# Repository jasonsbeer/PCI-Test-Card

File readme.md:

A card to connect test equipment to a 5V/Universal PCI bus slot.

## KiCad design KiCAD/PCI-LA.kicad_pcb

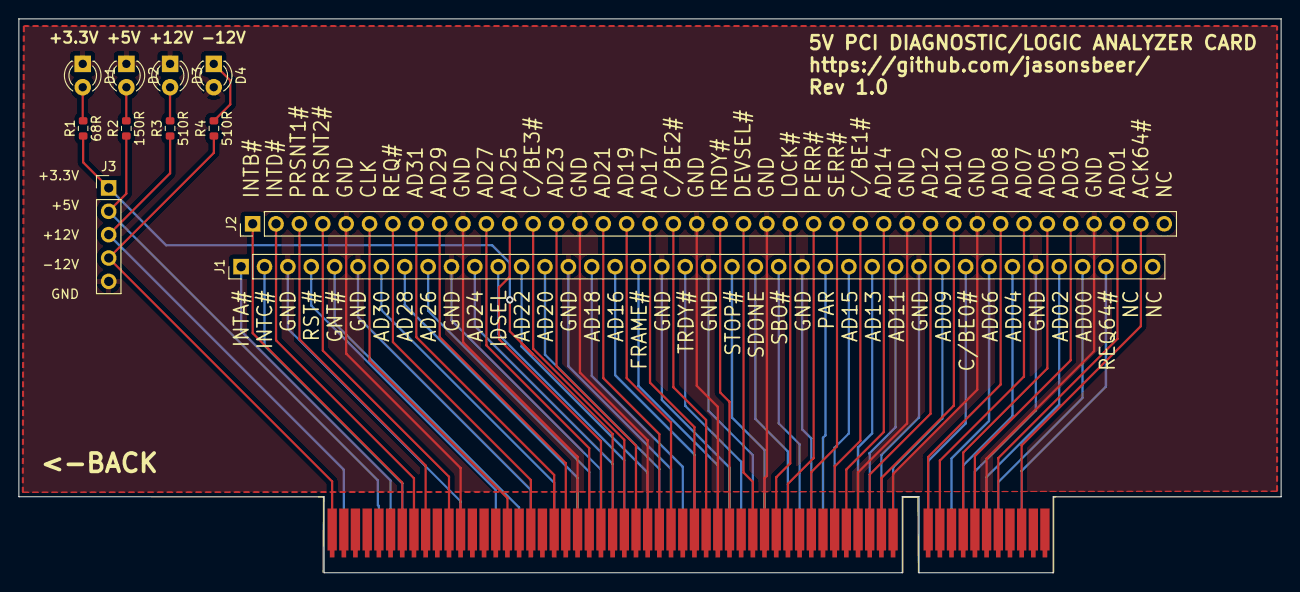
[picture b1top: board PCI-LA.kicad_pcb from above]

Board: 2 copper layers, 137.2 x 60.2 mm, 12 parts (0 on the bottom side), 69 nets.

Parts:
CN1: Bus_PCI_32bit_5V; BUS_PCI
D1, D2, D3, D4: LED; LED_D3.0mm
J1, J2: Conn_01x40; PinHeader_1x40_P2.54mm_Vertical
J3: Conn_01x05; PinHeader_1x05_P2.54mm_Vertical
R1: 68R; R_0603_1608Metric
R2: 150R; R_0603_1608Metric
R3, R4: 510R; R_0603_1608Metric

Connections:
+3.3V: CN1.B25 (+3.3V), J3.1, R1.1
+5V: CN1.A5 (+5V), J3.2, R2.1
+12V: CN1.A2 (+12V), J3.3, R3.1
-12V: CN1.B1 (-12V), J3.4, R4.2
/ACK64#: CN1.B60 (ACK64#), J2.39
/AD00: CN1.A58 (AD[00]), J1.37
/AD01: CN1.B58 (AD[01]), J2.38
/AD02: CN1.A57 (AD[02]), J1.36
/AD03: CN1.B56 (AD[03]), J2.36
/AD04: CN1.A55 (AD[04]), J1.34
/AD05: CN1.B55 (AD[05]), J2.35
/AD06: CN1.A54 (AD[06]), J1.33
/AD07: CN1.B53 (AD[07]), J2.34
/AD08: CN1.B52 (AD[08]), J2.33
/AD09: CN1.A49 (AD[09]), J1.31
/AD10: CN1.B48 (AD[10]), J2.31
/AD11: CN1.A47 (AD[11]), J1.29
/AD12: CN1.B47 (AD[12]), J2.30
/AD13: CN1.A46 (AD[13]), J1.28
/AD14: CN1.B45 (AD[14]), J2.28
/AD15: CN1.A44 (AD[15]), J1.27
/AD16: CN1.A32 (AD[16]), J1.17
/AD17: CN1.B32 (AD[17]), J2.18
/AD18: CN1.A31 (AD[18]), J1.16
/AD19: CN1.B30 (AD[19]), J2.17
/AD20: CN1.A29 (AD[20]), J1.14
/AD21: CN1.B29 (AD[21]), J2.16
/AD22: CN1.A28 (AD[22]), J1.13
/AD23: CN1.B27 (AD[23]), J2.14
/AD24: CN1.A25 (AD[24]), J1.11
/AD25: CN1.B24 (AD[25]), J2.12
/AD26: CN1.A23 (AD[26]), J1.9
/AD27: CN1.B23 (AD[27]), J2.11
/AD28: CN1.A22 (AD[28]), J1.8
/AD29: CN1.B21 (AD[29]), J2.9
/AD30: CN1.A20 (AD[30]), J1.7
/AD31: CN1.B20 (AD[31]), J2.8
/CLK: CN1.B16 (CLK), J2.6
/C/BE0#: CN1.A52 (C/BE#[0]), J1.32
/C/BE1#: CN1.B44 (C/BE#[1]), J2.27
/C/BE2#: CN1.B33 (C/BE#[2]), J2.19
/C/BE3#: CN1.B26 (C/BE#[3]), J2.13
/DEVSEL#: CN1.B37 (DEVSEL#), J2.22
/FRAME#: CN1.A34 (FRAME#), J1.18
/GNT#: CN1.A17 (GNT#), J1.5
/IDSEL: CN1.A26 (IDSEL), J1.12
/INTA#: CN1.A6 (INTA#), J1.1
/INTB#: CN1.B7 (INTB#), J2.1
/INTC#: CN1.A7 (INTC#), J1.2
/INTD#: CN1.B8 (INTD#), J2.2
/IRDY#: CN1.B35 (IRDY#), J2.21
/LOCK#: CN1.B39 (LOCK#), J2.24
/PAR: CN1.A43 (PAR), J1.26
/PERR#: CN1.B40 (PERR#), J2.25
/PRSNT1#: CN1.B9 (PRSNT1#), J2.3
/PRSNT2#: CN1.B11 (PRSNT2#), J2.4
/REQ64#: CN1.A60 (REQ64#), J1.38
/REQ#: CN1.B18 (REQ#), J2.7
/RST#: CN1.A15 (RST#), J1.4
/SBO#: CN1.A41 (SBO#), J1.24
/SDONE: CN1.A40 (SDONE), J1.23
/SERR#: CN1.B42 (SERR#), J2.26
/STOP#: CN1.A38 (STOP#), J1.22
/TRDY#: CN1.A36 (TRDY#), J1.20
GND: CN1.A12 (GND), CN1.A13 (GND), CN1.A18 (GND), CN1.A24 (GND), CN1.A30 (GND), CN1.A35 (GND), CN1.A37 (GND), CN1.A42 (GND), CN1.A48 (GND), CN1.A56 (GND), CN1.B12 (GND), CN1.B13 (GND), CN1.B15 (GND), CN1.B17 (GND), CN1.B22 (GND), CN1.B28 (GND), CN1.B34 (GND), CN1.B38 (GND), CN1.B46 (GND), CN1.B49 (GND), CN1.B57 (GND), D1.1 (K), D2.1 (K), D3.1 (K), D4.2 (A), J1.3, J1.6, J1.10, J1.15, J1.19, J1.21, J1.25, J1.30, J1.35, J2.5, J2.10, J2.15, J2.20, J2.23, J2.29, J2.32, J2.37, J3.5
unnamed: D1.2 (A), R1.2
unnamed: D2.2 (A), R2.2
unnamed: D3.2 (A), R3.2
unnamed: D4.1 (K), R4.1
